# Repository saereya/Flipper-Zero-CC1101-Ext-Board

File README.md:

# Flipper Zero External CC1101 PCB

A PCB that plugs onto the Flipper Zero GPIO header and carries an external
CC1101 sub-GHz module, so you can use a better antenna than the built-in radio.
It also brings out the Flipper signals the radio does not use, and has a
prototyping area for further development.

## V2 — current design

**[CC1101ExtBoardV2/](CC1101ExtBoardV2/)** — KiCad 10, 61.34 × 32.84 mm, two
layers, hand-solderable. ERC and DRC clean, schematic and board in parity, with
gerbers, drill, BOM, position file and reports committed.

The radio now runs from Flipper pin 9 (+3V3) through a series Schottky and a
ferrite bead — no regulator and no zener. Every one of the eighteen connector
pads carries a real net, GDO2 is broken out to pin 7, ESD arrays sit at the
connector, ground is poured on both layers, and the prototyping grid is a true
2.54 mm array with rails on real nets.

See [CC1101ExtBoardV2/README.md](CC1101ExtBoardV2/README.md) for the pin map,
the bill of materials, the setup step you need on the Flipper, and a full
account of what changed and why.

One correction worth flagging: the V1 review claimed the connector could not
mate with a Flipper Zero because the GPIO header is "two rows of nine". It is
not. The Flipper Zero GPIO is a single row of 18 pins, split 8 + 10 with a
17.78 mm gap, 58.42 mm from pad 1 to pad 18 — exactly what V1 had. That
geometry was right and V2 keeps it. Everything else in the review was real and
is fixed.

## V1 — original design

**[CC1101ExtBoard/](CC1101ExtBoard/)** — kept for reference. Do not build it:
its 3.6 V zener is fitted backwards across the supply, its regulator has input
and output on the same net, and the radio is fed from the Flipper's +5V pin.

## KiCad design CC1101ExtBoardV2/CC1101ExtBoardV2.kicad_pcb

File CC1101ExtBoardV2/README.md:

# CC1101 Ext Board V2

A Flipper Zero GPIO carrier for the common 8-pin CC1101 sub-GHz module, with a
prototyping area and a breakout for the Flipper signals the radio does not use.

61.34 × 32.84 mm, two layers, hand-solderable throughout (0805 passives, SOT-23-6,
SOD-123). ERC and DRC are clean; the only remaining DRC entries are silkscreen
overlap warnings where a connector's own pin labels sit close to its pads.

## Wiring

The Flipper Zero GPIO is a **single row of 18 pins**, split into an 8-pin group
(pins 1–8) and a 10-pin group (pins 9–18) with a 17.78 mm gap, 58.42 mm from
pad 1 to pad 18. J1 is the full 18-pin right-angle male header, so its pins bend
down past the mating edge into the Flipper's female sockets and the board lies in
the plane of the GPIO field.

| Flipper pin | Signal | Net on this board | CC1101 module | Notes |
|---|---|---|---|---|
| 1 | +5V | `+5V` | — | Breakout J4 pin 1 only. Off by default; enable it in the GPIO menu. |
| 2 | PA7 | `/MOSI` | MOSI (6) | Clamped by D2 |
| 3 | PA6 | `/MISO` | MISO (7) | Clamped by D2 |
| 4 | PA4 | `/CSN` | CSN (4) | Clamped by D3 |
| 5 | PB3 | `/SCK` | SCK (5) | Clamped by D3 |
| 6 | PB2 | `/GDO0` | GDO0 (3) | Clamped by D4 |
| 7 | PC3 | `/GDO2` | GDO2 (8) | Clamped by D4. V1 left this pin unused. |
| 8 | GND | `GND` | GND (1) | |
| 9 | +3V3 | `+3V3` | — | The only supply the radio uses. 1.2 A available. |
| 10 | SWC | `/SWC` | — | Breakout J4 pin 2 |
| 11 | GND | `GND` | — | |
| 12 | SIO | `/SIO` | — | Breakout J4 pin 3 |
| 13 | TX | `/TX` | — | Breakout J4 pin 4 |
| 14 | RX | `/RX` | — | Breakout J4 pin 5 |
| 15 | PC1 | `/PC1` | — | Breakout J4 pin 6 |
| 16 | PC0 | `/PC0` | — | Breakout J4 pin 7 |
| 17 | 1W | `/1W` | — | Breakout J4 pin 8 |
| 18 | GND | `GND` | — | Breakout J4 pin 9 |

All eighteen pads carry a net. No power pin is silenced with a no-connect flag.

## Power tree

```
J1.9 (+3V3, from the Flipper)
  └─ D1  PMEG2010EH        series Schottky, reverse and back-feed protection
      └─ +3V3_SYS          C1 10 µF, C2 100 nF, R1+D5 indicator, ESD array rails
          └─ FB1 600 R @ 100 MHz
              └─ +3V3_RF   C3 10 µF, C4 100 nF, J2 pin 2 (module VCC),
                           and the proto-area +3V3 rail
```

There is no regulator and no zener. The CC1101 operates from 1.8 V to 3.6 V with
an absolute maximum of 3.9 V, so the Flipper's own 3.3 V rail is the correct
supply; output power is set by PATABLE, not by supply voltage. Budget about
0.25 V of drop across D1 at the module's ~35 mA transmit current, leaving roughly
3.05 V at the socket.

## Using it

1. Plug the CC1101 module into J2. Pin 1 (GND) is the square pad, marked on the
   silkscreen; the module hangs over the board, clear of the 0805 passives.
2. Fit the board onto the Flipper's GPIO sockets. The 8 + 10 split is
   self-keying — it will not mate rotated.
3. On the Flipper: **Sub-GHz → Radio Settings → Module: External**.
4. D5 lights when the board has power. Nothing needs the +5V pin.

## Bill of materials

| Ref | Value | Package | Purpose |
|---|---|---|---|
| J1 | Flipper Zero GPIO | 1×08 + 1×10 right-angle **male pin header**, 2.54 mm | Plugs into the Flipper's female GPIO sockets |
| J2 | CC1101 module | 2×04 socket, 2.54 mm | Radio module |
| J3 | 50 pads, 2.54 mm | THT grid | Prototyping area, +3V3 and GND rails |
| J4 | Spare pins | 1×09 header, 2.54 mm | Breakout: +5V, SWC, SIO, TX, RX, PC1, PC0, 1W, GND |
| D1 | PMEG2010EH | SOD-123 | Series Schottky |
| D2–D4 | SRV05-4 | SOT-23-6 | ESD rail-clamp arrays, ~3 pF per line |
| D5 | LED (red) | 0805 | Power indicator |
| FB1 | 600 R @ 100 MHz | 0805 | Radio supply filter |
| C1, C3 | 10 µF | 0805 | Bulk, each side of FB1 |
| C2, C4 | 100 nF | 0805 | HF decoupling, each side of FB1 |
| R1 | 1 kΩ | 0805 | LED series resistor (~1.5 mA) |

`doc/bom.csv` is the generated version. J1 is **male** right-angle headers —
the Flipper Zero's GPIO is female. J2 is a female socket, because the CC1101
module has male pins.

## What changed from V1

Driven by the V1 design review. Every fix and the one finding that turned out to
be wrong:

| Errata item | V2 |
|---|---|
| PWR·1 reversed 3.6 V zener | Deleted. The Flipper regulates this rail. |
| PWR·2 regulator input and output on one net | LF33 deleted; the radio runs from Flipper pin 9. |
| PWR·3 radio fed from +5V | Supply is now pin 9 (+3V3) through D1 and FB1. |
| PWR·4 10 Ω LED resistor | R1 = 1 kΩ, about 1.5 mA. |
| **CONN·1 "connector cannot mate"** | **Wrong finding.** The Flipper GPIO really is one row of 18 split 8 + 10 over 58.42 mm, exactly as V1 had it. There is no 2×09 header. V1's connector geometry was correct and V2 keeps it. |
| SYNC·1 headers unannotated and unlinked | One annotated `J1` from the schematic, with a `path` back to its symbol. Schematic-parity check passes. |
| SYNC·2 no supply or ground return in the schematic | J1's supply pins are typed `power_out`; a PWR_FLAG marks the ground return. No no-connects on power pins. |
| SYNC·3 netless tracks and vias | Every track and via carries a net. Both prototyping rails are real nets that DRC checks. |
| MECH·1 prototyping grid off 0.1 inch | One footprint, true 2.54 mm in both axes, 10 × 5 pads plus two 10-pad rails. |
| FAB·1 objects outside the outline | Nothing outside the outline; copper-to-edge is an error at 0.3 mm. |
| FAB·2 zeroed design rules | Real rules: 0.15 mm clearance and track, 0.3 mm hole and edge, 0.05 mm mask expansion, 0.25 mm mask sliver. |
| BOM·1 LF33 symbol/value/footprint disagree | Regulator gone. Every remaining part's symbol, value and footprint agree. |
| GND·1 one ground pin, half a pour | All three Flipper grounds connected, GND poured on both layers with 10 stitching vias. |
| FUNC·1 GDO2 unused | GDO2 → Flipper pin 7 (PC3). |
| DOC·1 README overstates protection | This file: real wiring table, real protection, and the *Module: External* step. |
| REPO·1 generated files committed | `.gitignore` added at the repo root. Fab and documentation outputs are committed under `fab/` and `doc/`. |
| Rework step 3, ESD | Three SRV05-4 arrays, two channels each, so every clamp sits within about 2 mm of its connector pin. Six spare channels. |
| Rework step 7, current KiCad | KiCad 10 project throughout. |

## Layout notes and liberties taken

- **Mechanical reference.** J1's footprint is `FLIPPER-GPIO-18-RA` from
  [kbembedded/flipper-gpio-eda](https://github.com/kbembedded/flipper-gpio-eda)
  (BSD-2-Clause, see `library/LICENSE.flipper-gpio-eda`), which carries Flipper's
  own recommended board-edge profile on `User.Drawings`. The board outline traces
  it: the mating edge sits 3.84 mm below the pin row under each connector group
  and steps back to 1.24 mm across the gap, with 0.5 mm corner rounds.
  **Dry-fit before ordering** — the profile is from Flipper's published
  blueprint, not from a measured device.
- **3D models on J1.** Two edits to the upstream footprint, so the 3D preview is
  usable as a mechanical check. Upstream references a single eight-way model,
  unrotated, which lies *across* the pad row and covers only pads 1 and 9;
  replaced with both `PinHeader_1x08` and `PinHeader_1x10_P2.54mm_Horizontal` on
  the KiCad 10 model path, each rotated +90° about Z and offset by its own
  pin-field length. The rotation is needed because KiCad's standard 1×NN
  footprints run their pads along Y with the body on +X, while this footprint
  runs its pads along X with the body toward the mating edge; the offset slides
  each bar back over its own pads, since +90° also maps the pad axis onto −X.
  The only residual is that the pin-1 chamfer lands at the far end of each bar,
  which the square pad and silkscreen already mark correctly. The pads
  themselves were always a single row — this was a preview-only defect.
- **ESD split three ways.** A single SRV05-4 has its four I/O pads on only two
  x positions, which forces the SPI traces to cross to reach it. Three arrays let
  every tap be a straight stub off the connector pin, which is also what the
  part's own placement guidance asks for. The cost is six unused channels.
- **Series Schottky.** The errata asks for one. It is worth noting that the
  8 + 10 split makes a rotated mis-plug physically impossible, so D1's real value
  is blocking the board's 20 µF of bulk from back-feeding the Flipper's rail and
  surviving a partial insertion. If the 0.25 V drop matters more than that,
  fit a 0 Ω link in its place.
- **Module orientation.** J2 is placed so the module can overhang the top edge or
  lie over the board; nothing on the board is taller than 0.7 mm, and the socket
  raises the module about 8.5 mm. Which way the module body points depends on the
  module, so this has not been verified against a physical part.
- **Ground pour on both layers.** Signals are on F.Cu; +5V, and the three nets
  whose routing order does not match the module's pinout (`/CSN`, `/GDO2`, and the
  ESD rail feed), use short B.Cu runs.

## Files

```
CC1101ExtBoardV2.kicad_pro/_sch/_pcb   the design
library/CC1101ExtBoardV2.kicad_sym     project symbols
library/CC1101ExtBoardV2.pretty        project footprints
doc/                                   ERC, DRC, schematic PDF, renders, BOM, netlist
fab/                                   gerbers + drill (zipped), positions, STEP
build-outputs.sh                       regenerates everything in doc/ and fab/
```

`./build-outputs.sh` needs `kicad-cli` 10.x; it falls back to a
`~/.local/bin/kicad-*.AppImage` if `kicad-cli` is not on `PATH`, or set
`KICAD_CLI` yourself.

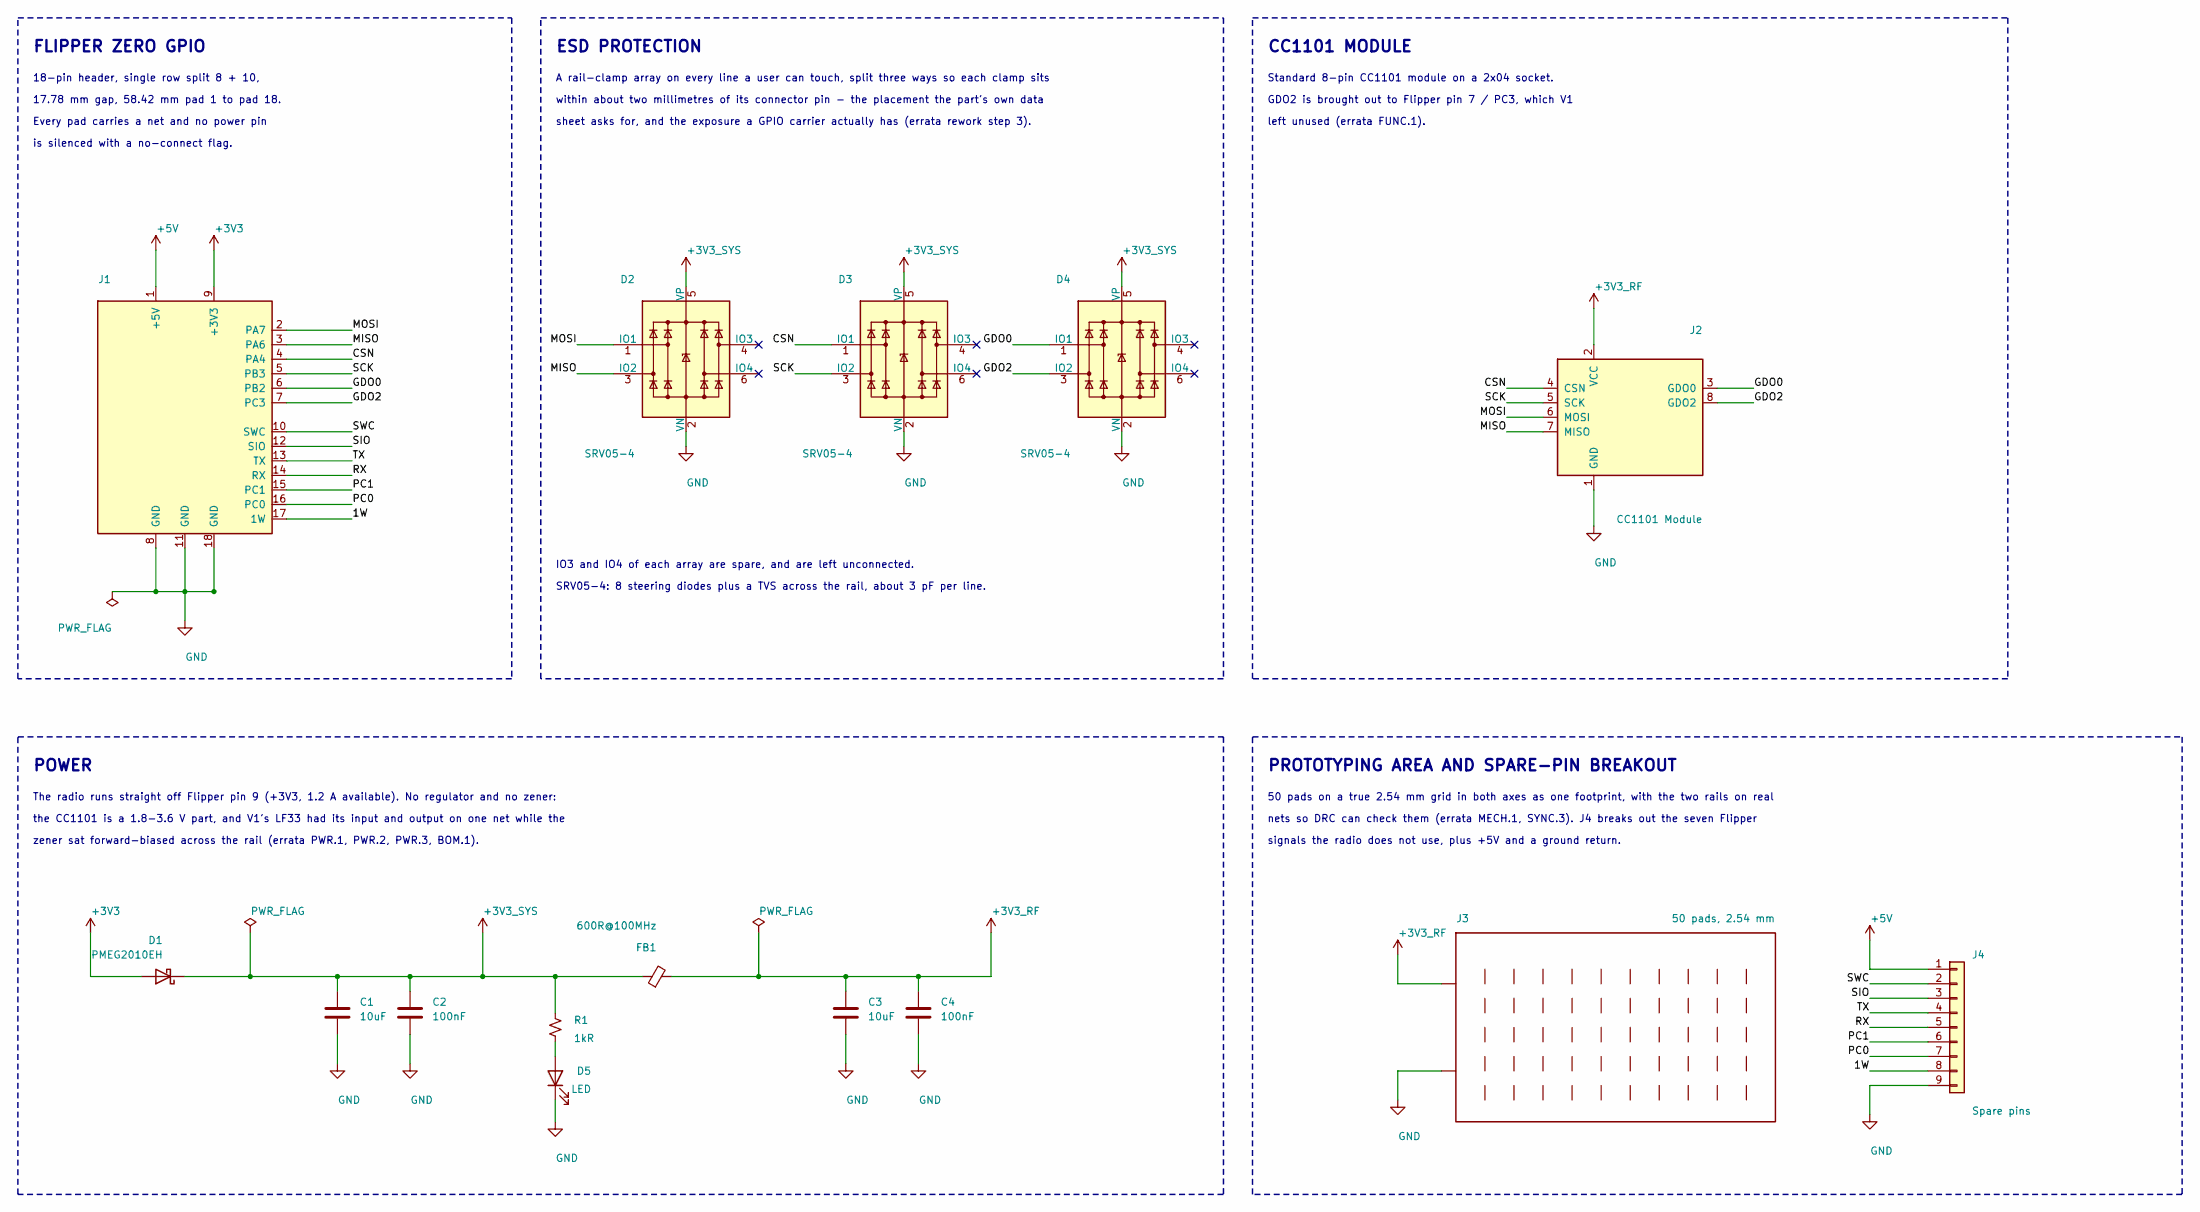
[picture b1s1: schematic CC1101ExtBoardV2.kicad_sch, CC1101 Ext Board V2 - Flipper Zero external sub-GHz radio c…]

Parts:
C1, C3: 10uF; C_0805_2012Metric_Pad1.18x1.45mm_HandSolder
C2, C4: 100nF; C_0805_2012Metric_Pad1.18x1.45mm_HandSolder
D1: PMEG2010EH; D_SOD-123
D2, D3, D4: SRV05-4; SOT-23-6_Handsoldering
D5: LED; LED_0805_2012Metric_Pad1.15x1.40mm_HandSolder
FB1: 600R@100MHz; L_0805_2012Metric_Pad1.05x1.20mm_HandSolder
J1: Flipper Zero GPIO; FLIPPER-GPIO-18-RA
J2: CC1101 Module; PinSocket_2x04_P2.54mm_Vertical
J3: 50 pads, 2.54 mm; ProtoGrid_10x5_P2.54mm
J4: Spare pins; PinHeader_1x09_P2.54mm_Vertical
R1: 1kR; R_0805_2012Metric_Pad1.20x1.40mm_HandSolder

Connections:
+3V3: D1.2 (A), J1.9 (+3V3)
+3V3_RF: C3.1, C4.1, FB1.2, J2.2 (VCC), J3.51 (+3V3_RF)
+3V3_SYS: C1.1, C2.1, D1.1 (K), D2.5 (VP), D3.5 (VP), D4.5 (VP), FB1.1, R1.1
+5V: J1.1 (+5V), J4.1
/1W: J1.17 (1W), J4.8
/CSN: D3.1 (IO1), J1.4 (PA4), J2.4 (CSN)
/GDO0: D4.1 (IO1), J1.6 (PB2), J2.3 (GDO0)
/GDO2: D4.3 (IO2), J1.7 (PC3), J2.8 (GDO2)
/MISO: D2.3 (IO2), J1.3 (PA6), J2.7 (MISO)
/MOSI: D2.1 (IO1), J1.2 (PA7), J2.6 (MOSI)
/PC0: J1.16 (PC0), J4.7
/PC1: J1.15 (PC1), J4.6
/RX: J1.14 (RX), J4.5
/SCK: D3.3 (IO2), J1.5 (PB3), J2.5 (SCK)
/SIO: J1.12 (SIO), J4.3
/SWC: J1.10 (SWC), J4.2
/TX: J1.13 (TX), J4.4
GND: C1.2, C2.2, C3.2, C4.2, D2.2 (VN), D3.2 (VN), D4.2 (VN), D5.1 (K), J1.8 (GND), J1.11 (GND), J1.18 (GND), J2.1 (GND), J3.52 (GND), J4.9
unnamed: D5.2 (A), R1.2

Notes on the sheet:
IO3 and IO4 of each array are spare, and are left unconnected.
A rail-clamp array on every line a user can touch, split three ways so each clamp sits
nets so DRC can check them (errata MECH.1, SYNC.3). J4 breaks out the seven Flipper
FLIPPER ZERO GPIO
the CC1101 is a 1.8-3.6 V part, and V1's LF33 had its input and output on one net while the
18-pin header, single row split 8 + 10,
POWER
is silenced with a no-connect flag.
within about two millimetres of its connector pin - the placement the part's own data
CC1101 MODULE
Standard 8-pin CC1101 module on a 2x04 socket.
sheet asks for, and the exposure a GPIO carrier actually has (errata rework step 3).
GDO2 is brought out to Flipper pin 7 / PC3, which V1
zener sat forward-biased across the rail (errata PWR.1, PWR.2, PWR.3, BOM.1).
50 pads on a true 2.54 mm grid in both axes as one footprint, with the two rails on real
SRV05-4: 8 steering diodes plus a TVS across the rail, about 3 pF per line.
PROTOTYPING AREA AND SPARE-PIN BREAKOUT
signals the radio does not use, plus +5V and a ground return.
The radio runs straight off Flipper pin 9 (+3V3, 1.2 A available). No regulator and no zener:
17.78 mm gap, 58.42 mm pad 1 to pad 18.
left unused (errata FUNC.1).
ESD PROTECTION
Every pad carries a net and no power pin

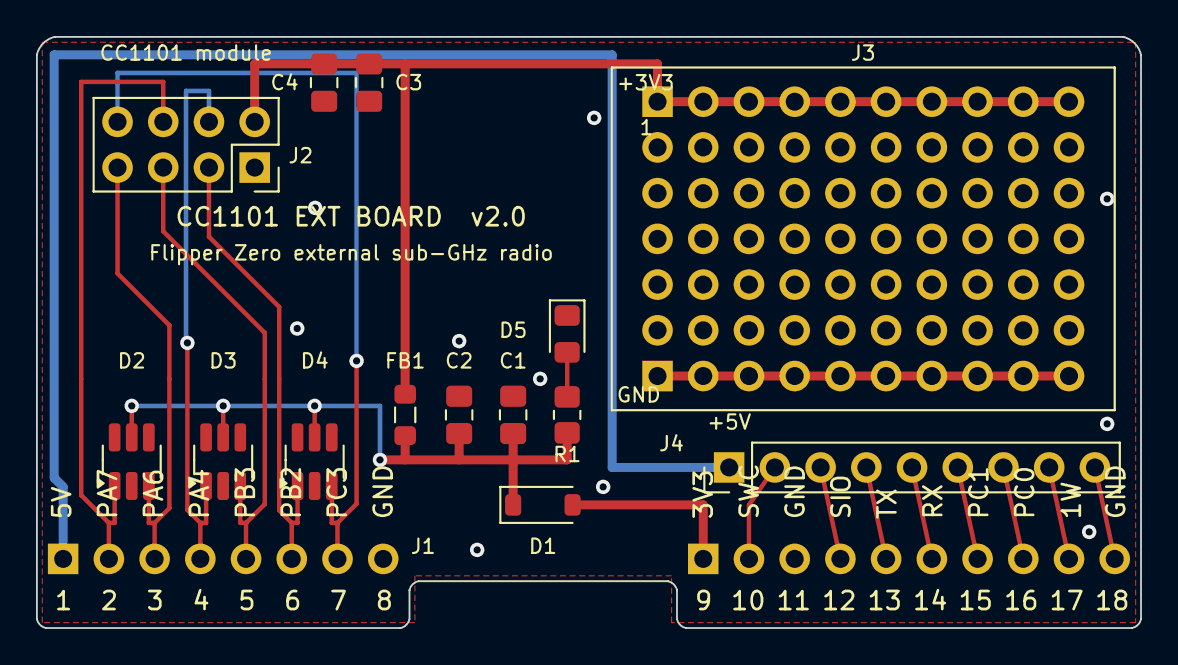
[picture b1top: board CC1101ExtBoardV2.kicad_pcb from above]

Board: 2 copper layers, 61.3 x 32.8 mm, 15 parts (0 on the bottom side), 19 nets.

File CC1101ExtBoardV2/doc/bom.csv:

"Refs","Value","Footprint","Qty","Datasheet"
"C1,C3","10uF","Capacitor_SMD:C_0805_2012Metric_Pad1.18x1.45mm_HandSolder","2",""
"C2,C4","100nF","Capacitor_SMD:C_0805_2012Metric_Pad1.18x1.45mm_HandSolder","2",""
"D1","PMEG2010EH","Diode_SMD:D_SOD-123","1",""
"D2-D4","SRV05-4","Package_TO_SOT_SMD:SOT-23-6_Handsoldering","3",""
"D5","LED","LED_SMD:LED_0805_2012Metric_Pad1.15x1.40mm_HandSolder","1",""
"FB1","600R@100MHz","Inductor_SMD:L_0805_2012Metric_Pad1.05x1.20mm_HandSolder","1",""
"J1","Flipper Zero GPIO","CC1101ExtBoardV2:FLIPPER-GPIO-18-RA","1","https://docs.flipper.net/zero/gpio-and-modules"
"J2","CC1101 Module","Connector_PinSocket_2.54mm:PinSocket_2x04_P2.54mm_Vertical","1",""
"J3","50 pads, 2.54 mm","CC1101ExtBoardV2:ProtoGrid_10x5_P2.54mm","1",""
"J4","Spare pins","Connector_PinHeader_2.54mm:PinHeader_1x09_P2.54mm_Vertical","1",""
"R1","1kR","Resistor_SMD:R_0805_2012Metric_Pad1.20x1.40mm_HandSolder","1",""
